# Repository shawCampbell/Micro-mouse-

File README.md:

# Micro-mouse-
Development of the sensing and power subsystems of a micro-mouse.

This project concerns designing an infrared sensor subsystem and power subsystem with an existing micro-mouse motherboard and housing. This 
project uses the STM32L476 microcontroller and two motors.

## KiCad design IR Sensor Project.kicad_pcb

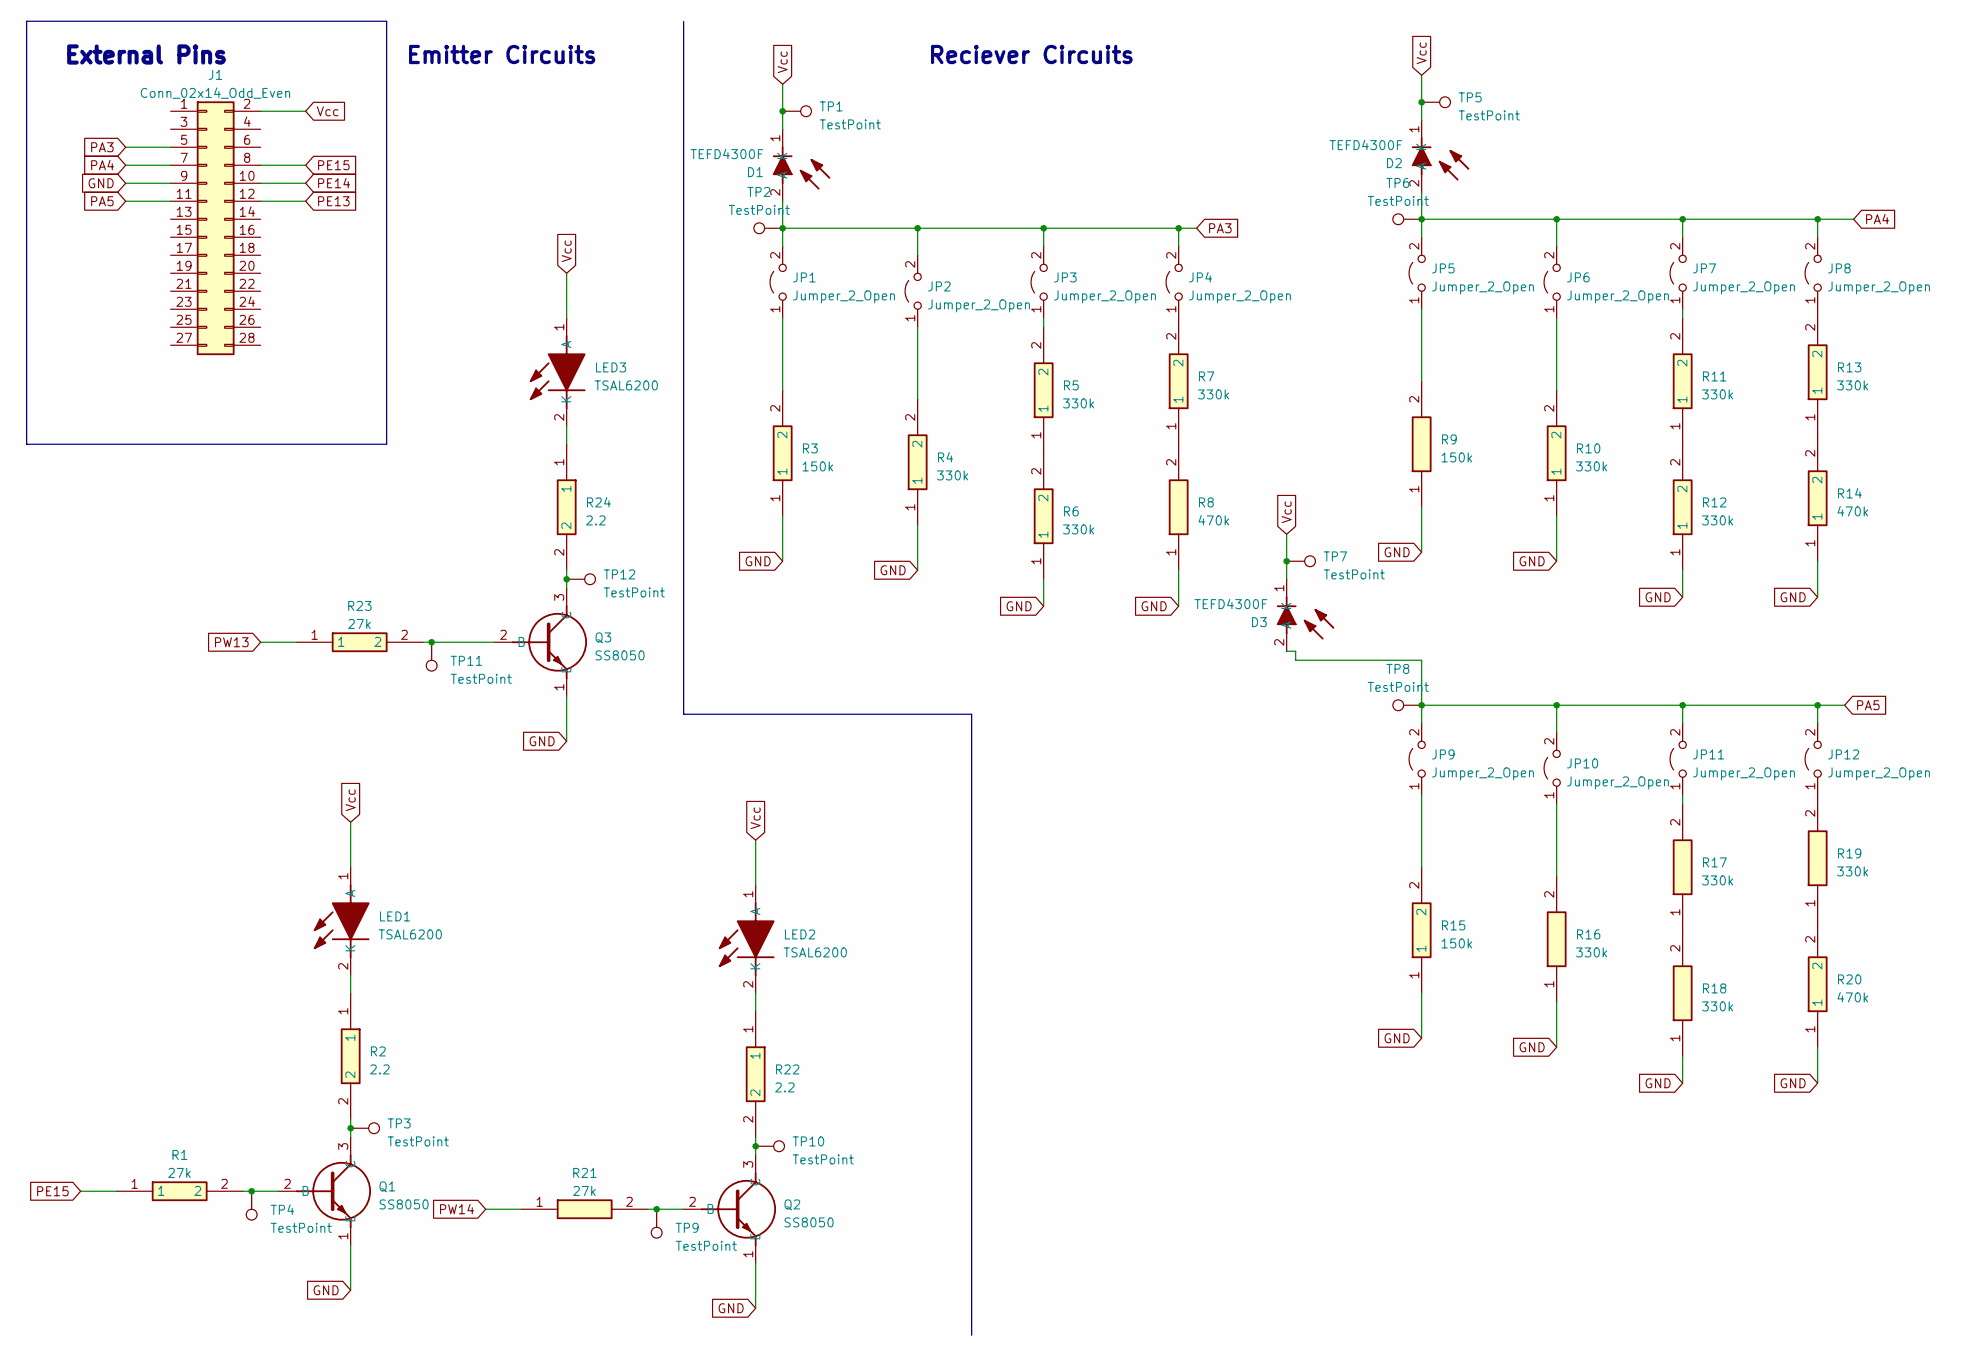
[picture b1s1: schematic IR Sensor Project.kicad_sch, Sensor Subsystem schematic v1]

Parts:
D1, D2, D3: TEFD4300F; Manufacturer_Part_Number TEFD4300F; Mouser Part Number 78-TEFD4300F
J1: Conn_02x14_Odd_Even; PinHeader_2x14_P2.54mm_Vertical
JP1, JP2, JP3, JP4, JP5, JP6, JP7, JP8, JP9, JP10, JP11, JP12: Jumper_2_Open; TestPoint_2Pads_Pitch2.54mm_Drill0.8mm
LED1, LED2, LED3: TSAL6200; Manufacturer_Part_Number TSAL6200; Mouser Part Number 782-TSAL6200
Q1, Q2, Q3: SS8050; Manufacturer_Part_Number SS8050; Mouser Part Number N/A
R1, R21, R23: 27k; RESC2013X65N; Manufacturer_Part_Number 0805W8F2702T5E; LCSC 0805W8F2702T5E
R2, R22, R24: 2.2; RESC2013X65N; Manufacturer_Part_Number 0805W8F220KT5E; Mouser Part Number 303-0805W8F220KT5E
R3, R9, R15: 150k; RESC1608X55N; Manufacturer_Part_Number 0603WAF1503T5E; LCSC 0603WAF1503T5E
R4, R10, R16: 330k; RESC1608X55N; Manufacturer_Part_Number 0603WAF3303T5E; LCSC 0603WAF3303T5E
R5, R6, R7, R11, R12, R13, R17, R18, R19: 330k; RESC1608X55N; Manufacturer_Part_Number 0603WAF1503T5E; LCSC 0603WAF1503T5E
R8, R14, R20: 470k; RESC1608X55N; Manufacturer_Part_Number 0603WAF4703T5E; LCSC 0603WAF4703T5E
TP1, TP2, TP3, TP4, TP5, TP6, TP7, TP8, TP9, TP10, TP11, TP12: TestPoint; TestPoint_Pad_2.0x2.0mm

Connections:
GND: J1.9, Q1.1 (E), Q2.1 (E), Q3.1 (E), R3.1, R4.1, R6.1, R8.1, R9.1, R10.1, R12.1, R14.1, R15.1, R16.1, R18.1, R20.1
unnamed: JP1.1 (A), R3.2
unnamed: JP2.1 (A), R4.2
unnamed: JP3.1 (A), R5.2
unnamed: JP4.1 (A), R7.2
unnamed: JP5.1 (A), R9.2
unnamed: JP6.1 (A), R10.2
unnamed: JP7.1 (A), R11.2
unnamed: JP8.1 (A), R13.2
unnamed: JP9.1 (A), R15.2
unnamed: JP10.1 (A), R16.2
unnamed: JP11.1 (A), R17.2
unnamed: JP12.1 (A), R19.2
unnamed: LED1.2 (K), R2.1
unnamed: LED2.2 (K), R22.1
unnamed: LED3.2 (K), R24.1
unnamed: Q1.2 (B), R1.2, TP4.1
unnamed: Q1.3 (C), R2.2, TP3.1
unnamed: Q2.2 (B), R21.2, TP9.1
unnamed: Q2.3 (C), R22.2, TP10.1
unnamed: Q3.2 (B), R23.2, TP11.1
unnamed: Q3.3 (C), R24.2, TP12.1
unnamed: R5.1, R6.2
unnamed: R7.1, R8.2
unnamed: R11.1, R12.2
unnamed: R13.1, R14.2
unnamed: R17.1, R18.2
unnamed: R19.1, R20.2
PA3: D1.2 (A), J1.5, JP1.2 (B), JP2.2 (B), JP3.2 (B), JP4.2 (B), TP2.1
PA4: D2.2 (A), J1.7, JP5.2 (B), JP6.2 (B), JP7.2 (B), JP8.2 (B), TP6.1
PA5: D3.2 (A), J1.11, JP9.2 (B), JP10.2 (B), JP11.2 (B), JP12.2 (B), TP8.1
PE13: J1.12
PE14: J1.10
PE15: J1.8, R1.1
PW13: R23.1
PW14: R21.1
Vcc: D1.1 (K), D2.1 (K), D3.1 (K), J1.2, LED1.1 (A), LED2.1 (A), LED3.1 (A), TP1.1, TP5.1, TP7.1

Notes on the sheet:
Emitter Circuits
External Pins
Reciever Circuits

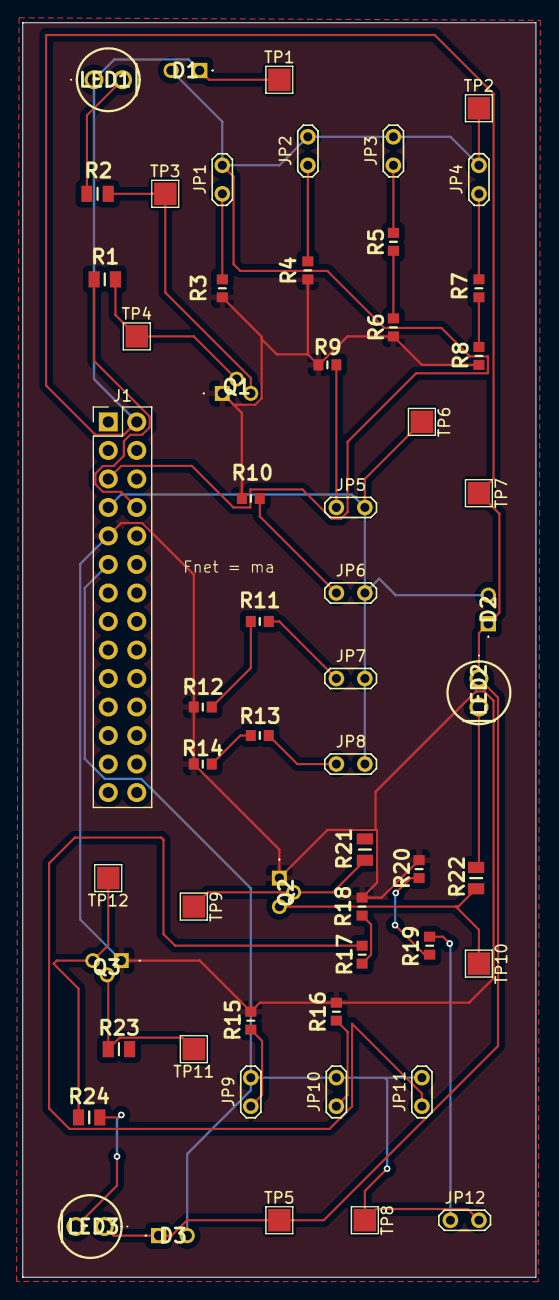
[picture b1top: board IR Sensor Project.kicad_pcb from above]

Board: 2 copper layers, 45.7 x 111.8 mm, 58 parts (0 on the bottom side), 33 nets.

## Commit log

2024-04-20 Add files via upload
    Assignment Brief
2024-04-20 Create Sensor Subsystem
    Files concerning the sensor subsystem of the micro-mouse.
2024-04-20 Create Notes
2024-04-20 Rename readme diagram.png to readme_diagram.png

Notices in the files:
IR Sensor Project.kicad_pcb:
creativecommons.org
Licence: CC BY 4.4
